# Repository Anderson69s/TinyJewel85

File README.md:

# TinyJewel85

A little board that allow you to customise a necklace or a jewel.

## Getting Started

These instructions will help you to use and change the behavior of the LED on your TinyJewel85.

### Pre-requisites

```
Arduino IDE > 1.5.8
```
```
Adafruit NeoPixel Librairy
```
```
Add ATTINY85 board to Arduino IDE
```

### Installing

A step by step tutorial is on my site : https://atelierdumaker.com/portfolio/tinyjewel85/

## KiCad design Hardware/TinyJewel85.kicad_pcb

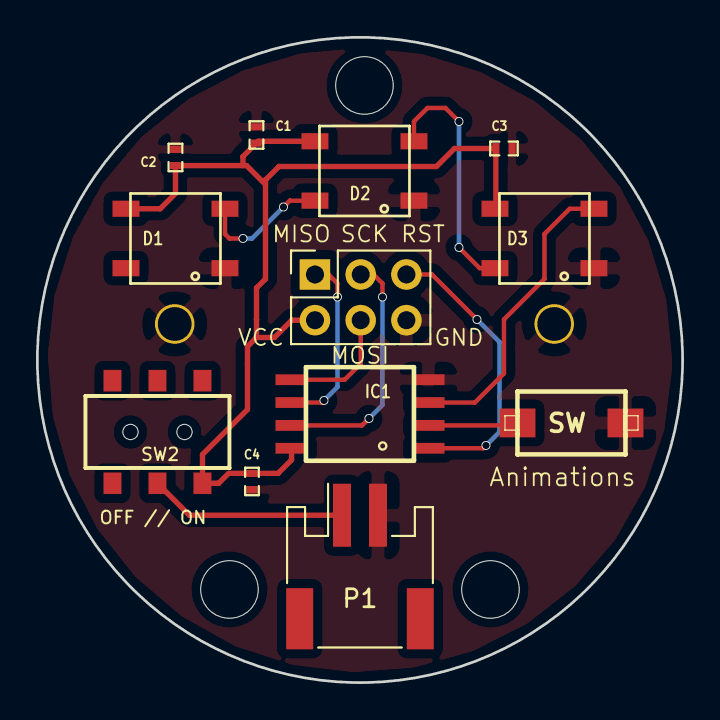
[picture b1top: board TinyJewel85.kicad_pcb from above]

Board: 2 copper layers, 35.8 x 35.8 mm, 10 parts (0 on the bottom side), 6 nets.

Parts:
C1, C2, C3, C4: SM0402
D1, D2, D3: WS2812B
IC1: SOIC8-W
SW: SWITCH_CMS
SW2: OFF // ON; Switch_DPDT

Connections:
+3V3: C1.1, C2.1, C3.1, C4.1, D1.1, D2.1, D3.1, IC1.8, SW2.1
GND: C1.2, C2.2, C3.2, C4.2, D1.3, D2.3, D3.3, IC1.4, SW.2
unnamed: D1.4, D2.2
unnamed: D2.4, D3.2
PB3: IC1.2, SW.1
PB4: D3.4, IC1.3

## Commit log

2017-08-11 Initial Commit
    First Realease
2017-09-23 2nd
    Everything ouut the loop
2018-05-16 Update Kicad
    Jump from 4.0.6 to 4.0.7
